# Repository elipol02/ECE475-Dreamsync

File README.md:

# Dreamsync

## Project Overview
Our product Dreamsync is designed to enhance health monitoring by integrating sensors that track various metrics related to sleep quality and environmental conditions. Data collected from the sensors are transmitted to a companion mobile application via Bluetooth for analysis and visualization. This will make it easier for our users to track their sleeping patterns.

### Features
- **Sleep Movement Monitoring**: Tracks body movements during sleep using an MPU6050 accelerometer and gyroscope.
- **Heart Rate Monitoring**: Continuously monitors heart rate using a photoplethysmography (PPG) sensor.
- **Environmental Light Exposure**: Measures light levels in the sleep environment using light sensors.
- **Ambient Temperature Monitoring**: Tracks the ambient temperature using a DS18B20 temperature sensor.
- **Battery Monitoring**: Measures battery voltage, percentage, and charging status.
- **Bluetooth Connectivity**: Transmits real-time sensor data to a companion app via BLE (Bluetooth Low Energy).

---

## Components and Dependencies

### Hardware Components
- **MPU6050**: Accelerometer and gyroscope for motion tracking.
- **DS18B20**: Temperature sensor.
- **PPG Sensor**: For heart rate monitoring.
- **Light Sensors**: Measures light levels (connected to analog pins A0 and A1).
- **nRF52840 Feather**: For Bluetooth communication.
- **LED**: Visual feedback for heart rate peaks.

### Software Libraries
- **Wire**: I2C communication with MPU6050.
- **OneWire**: Communication protocol for DS18B20.
- **DallasTemperature**: Interface for DS18B20 temperature sensor.
- **Adafruit Bluefruit**: Bluetooth communication.
- **Adafruit LittleFS**: Internal file system for configuration storage.

---

## Setup Instructions

### Hardware Setup
1. Connect the **MPU6050** to the I2C pins (SDA, SCL).
2. Attach the **DS18B20** sensor to `TEMP_SENSOR_PIN` (A2).
3. Connect **PPG Sensor** to `HEART_RATE_PIN` (A3).
4. Connect light sensors to `LIGHT_SENSOR_1` (A0) and `LIGHT_SENSOR_2` (A1).
5. Connect the LED to `LED_PIN` (3).

### Software Setup
1. You'll need to install the libraries we listed above.
2. Upload the firmware code provided to your nRF52840 development board via Arduino IDE.

### Mobile Application
1. Ensure the Bluetooth is enabled on your mobile device.
2. Pair with the "SleepMask" device via BLE.
3. Use the companion app to visualize and analyze the collected data.

---

## Code Highlights

### Key Functions
- **`initializeMPU6050()`**: Initializes the MPU6050 for motion tracking.
- **`readLightAndTemp()`**: Reads ambient light and temperature values.
- **`readHeartRateSensor()`**: Reads and processes heart rate data.
- **`calculateBPM()`**: Calculates beats per minute (BPM) based on PPG data.
- **`sendEnvironmentalData()`**: Sends light and temperature data over BLE.
- **`checkBattery()`**: Monitors battery voltage and percentage.
- **`startAdv()`**: Configures and starts BLE advertising.

### BLE Services
- **Device Information Service**: Provides metadata about the device.
- **UART Service**: Transmits sensor data to the mobile app.
- **Battery Service**: Sends battery status updates.

---

## Sensor Data Format

The sensor data is transmitted to the companion app in the following format:
1. **Environmental Data**: `E,light1,light2,temperature`
2. **Heart Rate Data**: `H,heartRate`
3. **Motion Data**: `M,accelX,accelY,accelZ,gyroX,gyroY,gyroZ,pitch,roll,motionIntensity`
4. **Battery Data**: `B,batteryVoltage,batteryPercent,isCharging`

---

## Contributors

Chukwuemeka Mordi, Chu-en Chang, Elijah Pollack, Kinner Parikh

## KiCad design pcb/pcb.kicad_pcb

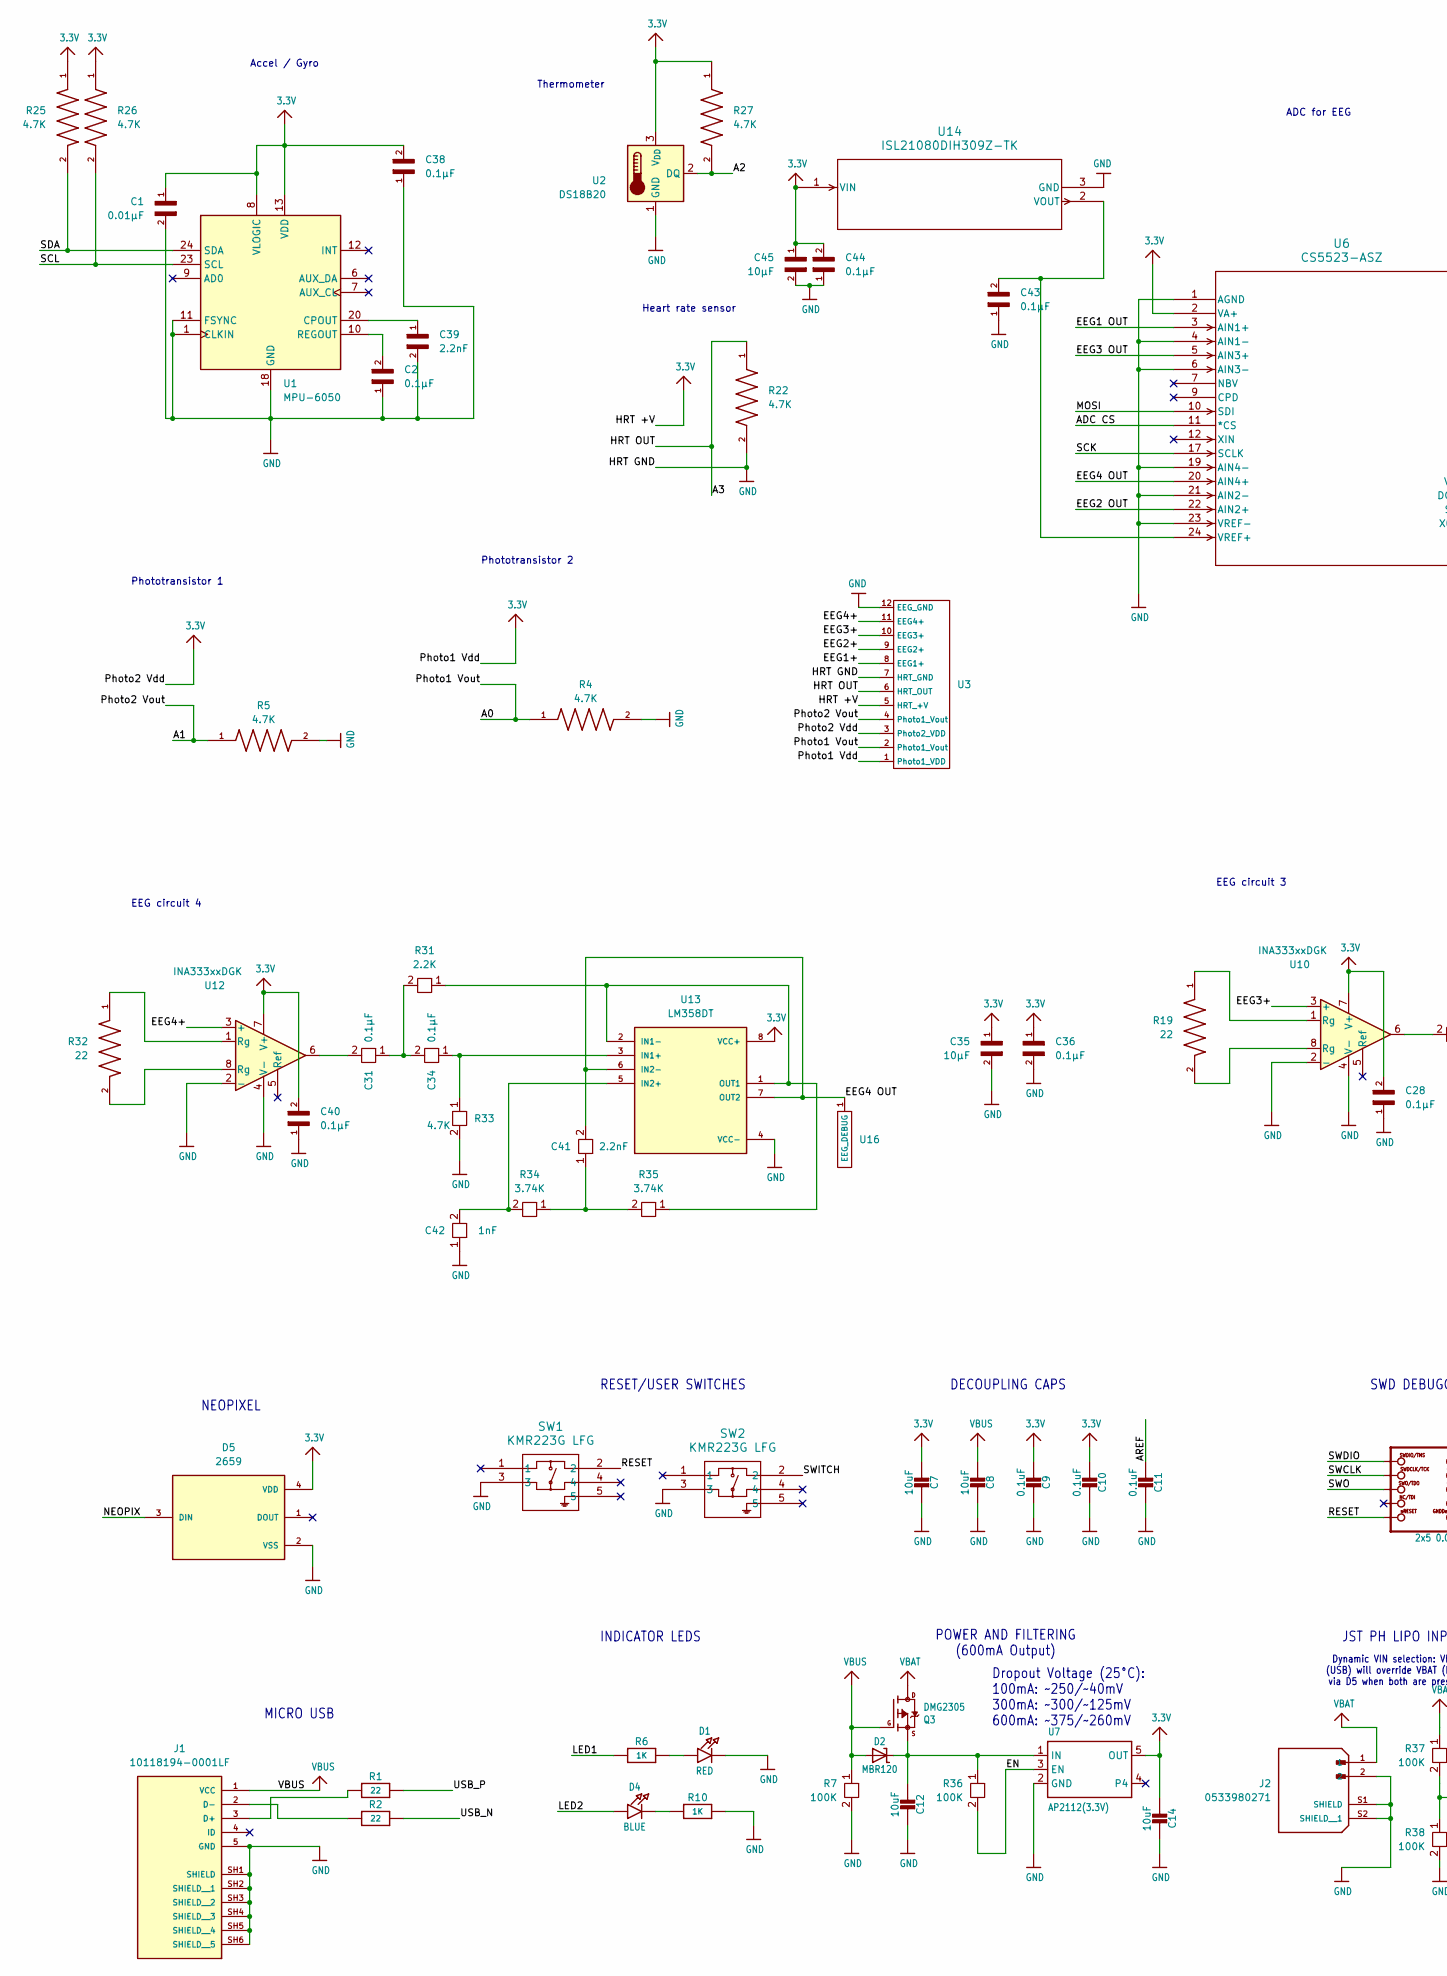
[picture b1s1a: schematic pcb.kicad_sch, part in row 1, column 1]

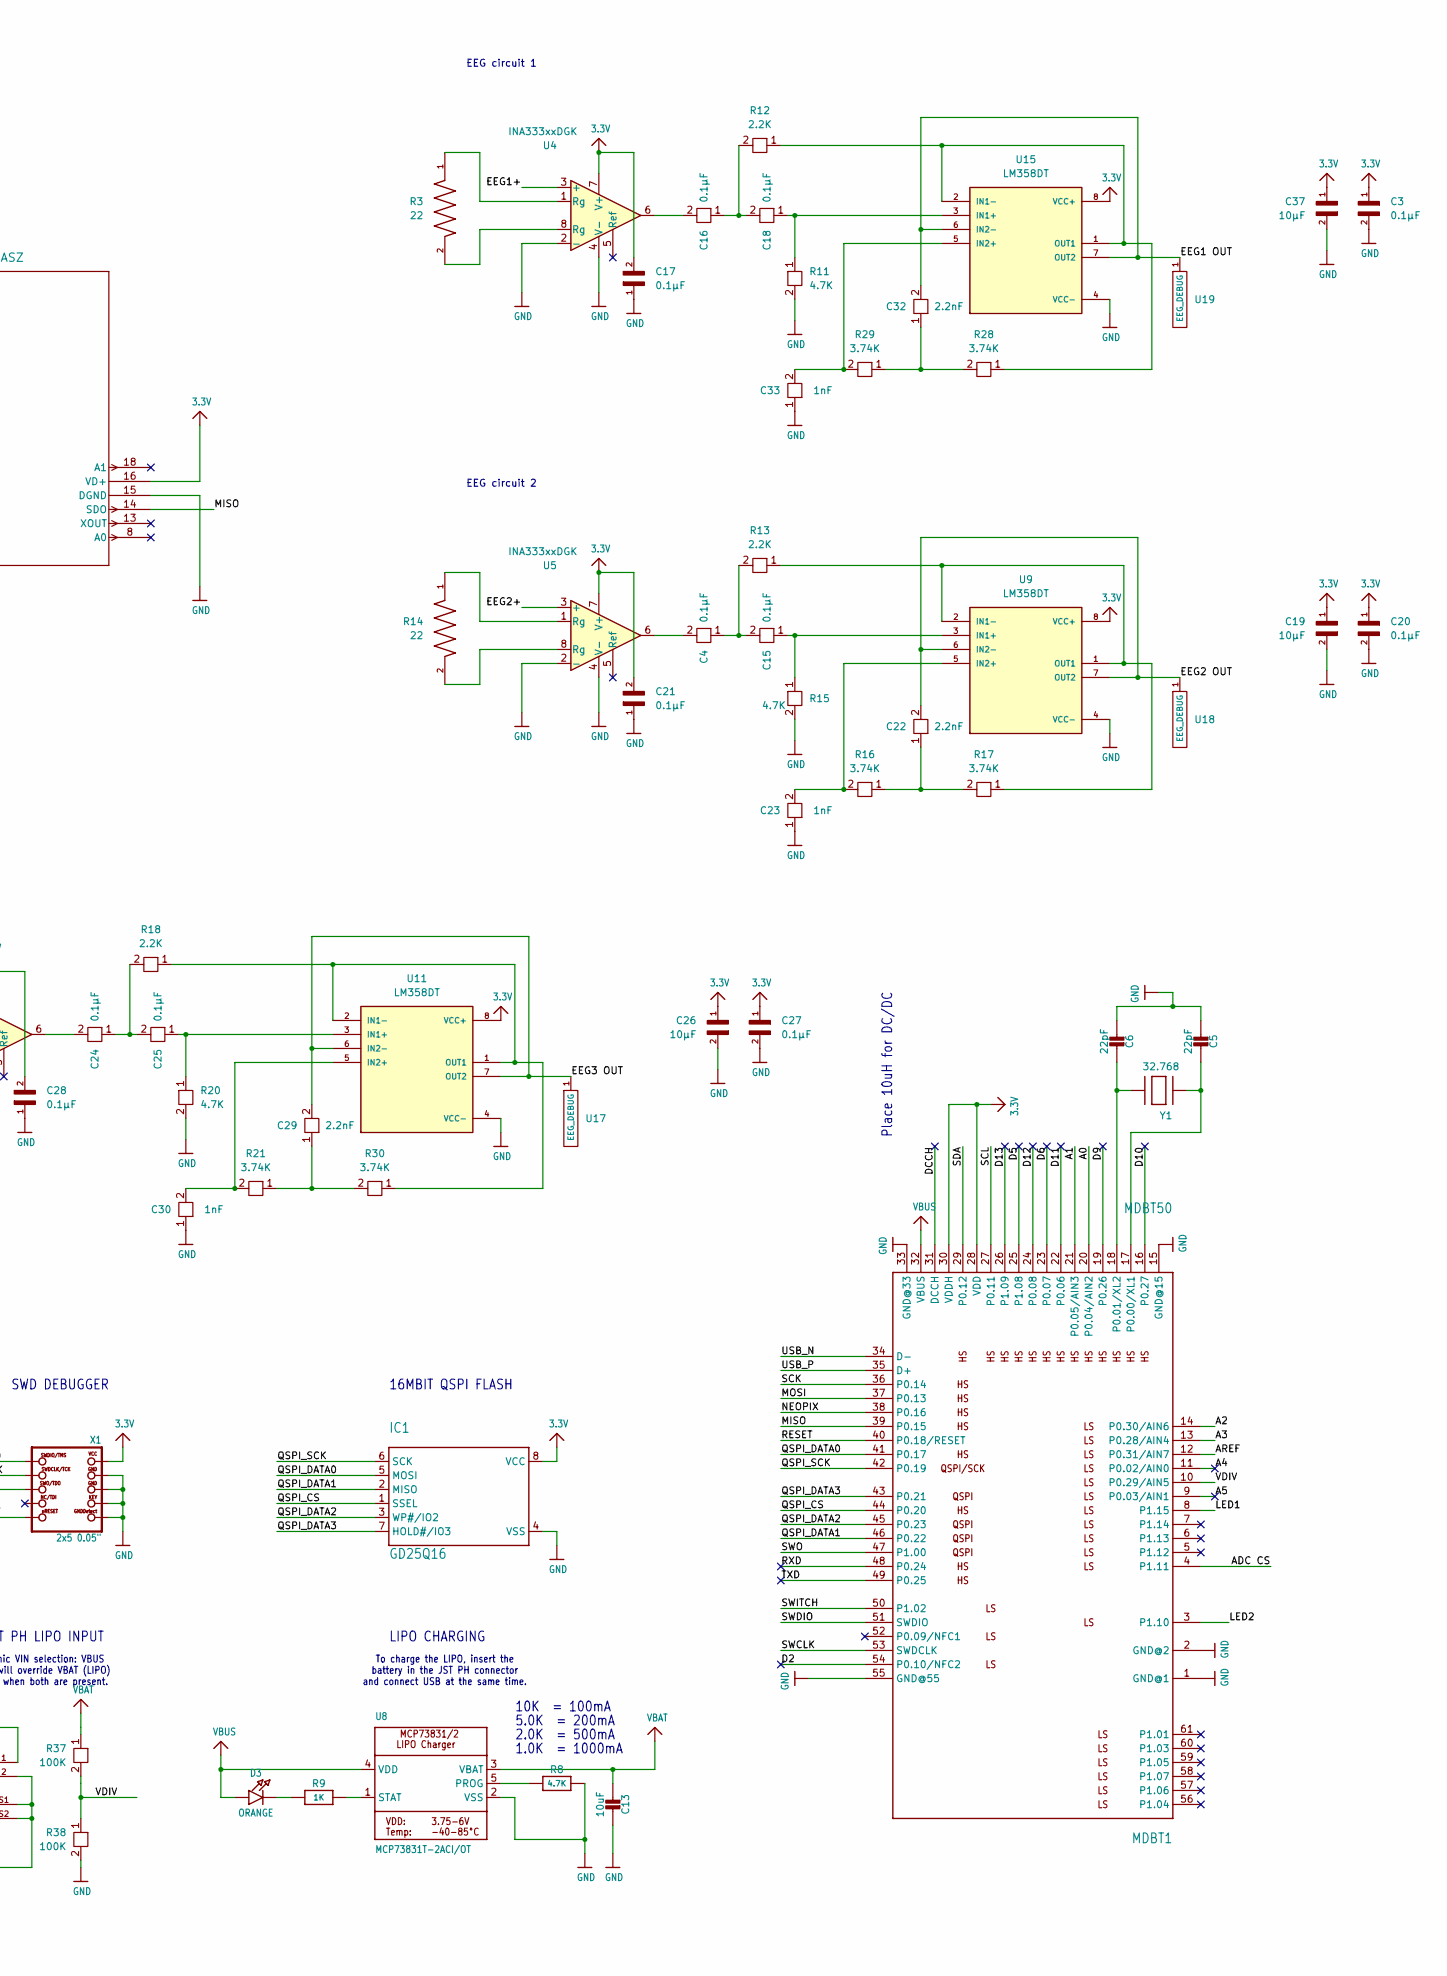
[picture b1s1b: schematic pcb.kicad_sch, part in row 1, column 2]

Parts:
C1: 0.01μF; CAPC2012X95N
C2, C3, C4, C15, C16, C17, C18, C20, C21, C24, C25, C27, C28, C31, C34, C36, C38, C40, C43, C44: 0.1μF; CAPC2012X88N
C5, C6: 22pF; CAPC220145_88N_KEM
C7, C8, C12, C13, C14: 10uF; CAPC2012X88N
C9, C10, C11: 0.1uF; CAPC2012X88N
C19, C26, C35, C37, C45: 10μF; CAPC2012X88N
C22, C29, C32, C39, C41: 2.2nF; CAP_CL21_SAM
C23, C30, C33, C42: 1nF; CAP_0805J_AVX
D1: RED; WL-SMCW_0805
D2: MBR120; SDO_SOD-123FL498_OSI
D3: ORANGE; WL-SMCW_0805
D4: BLUE; WL-SMCW_0805
D5: 2659; PARTREV 01
IC1: GD25Q16; SOIC127P600X175-8N
J1: 10118194-0001LF; AMPHENOL_10118194-0001LF; PARTREV D
J2: 0533980271; MOLEX_0533980271; PARTREV A
MDBT1: MDBT50; MDBT50Q-U
Q3: DMG2305; SOT91P240X110-3N_DMG2305UX-7
R1, R2, R3, R14, R19, R32: 22; RESC2012X60N
R4, R5, R22, R25, R26, R27: 4.7K; RESC2012X60N; DigiKey_Part_Number 311-4.7KJRTR-ND
R6, R9, R10: 1K; RESC2012X60N
R7, R36, R37, R38: 100K; RESC2012X60N
R8, R11, R15, R20, R33: 4.7K; RESC2012X60N
R12, R13, R18, R31: 2.2K; RESC2012X60N
R16, R17, R21, R28, R29, R30, R34, R35: 3.74K; RESC2012X60N
SW1, SW2: KMR223G LFG; KMR2_G_CNK
U1: MPU-6050; InvenSense_QFN-24_4x4mm_P0.5mm
U2: DS18B20; TO-92_Inline
U3: Sensors
U4, U5, U10, U12: INA333xxDGK; SOP65P490X110-8N
U6: CS5523-ASZ; CIR-SSOP-24
U7: AP2112(3.3V); SOT_RG1_DIO
U8: MCP73831T-2ACI/OT; SOT-23-5_MC_MCH
U9, U11, U13, U15: LM358DT; SOIC127P600X175-8N
U14: ISL21080DIH309Z-TK; P3_064_INR
U16, U17, U18, U19: EEG_DEBUG
X1: 2x5 0.05"; 2X05_1.27MM_BOX_POSTS
Y1: 32.768; XTAL_SC32S-7PF20PPM_EPS

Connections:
3.3V: C1.1, C3.1, C7.2, C9.2, C10.2, C14.2, C17.2, C19.1, C20.1, C21.2, C26.1, C27.1, C28.2, C35.1, C36.1, C37.1, C38.2, C40.2, C44.2, C45.1, D5.4 (VDD), IC1.8 (VCC), MDBT1.28 (VDD), MDBT1.30 (VDDH), R25.1, R26.1, R27.1, U1.8 (VLOGIC), U1.13 (VDD), U2.3 (V_{DD}), U3.1 (Photo1_VDD), U3.3 (Photo2_VDD), U3.5 (HRT_+V), U4.7 (V+), U5.7 (V+), U6.2 (VA+), U6.16 (VD+), U7.5 (OUT), U9.8 (VCC+), U10.7 (V+), U11.8 (VCC+), U12.7 (V+), U13.8 (VCC+), U14.1 (VIN), U15.8 (VCC+), X1.1 (VCC)
/A0: MDBT1.20 (P0.04/AIN2), R4.1, U3.2 (Photo1_Vout)
/A1: MDBT1.21 (P0.05/AIN3), R5.1, U3.4 (Photo1_Vout)
/A2: MDBT1.14 (P0.30/AIN6), R27.2, U2.2 (DQ)
/A3: MDBT1.13 (P0.28/AIN4), R22.1, U3.6 (HRT_OUT)
/A4: MDBT1.11 (P0.02/AIN0)
/A5: MDBT1.9 (P0.03/AIN1)
/ADC CS: MDBT1.4 (P1.11), U6.11 (*CS)
/AREF: C11.2, MDBT1.12 (P0.31/AIN7)
/D2: MDBT1.54 (P0.10/NFC2)
/D5: MDBT1.25 (P1.08)
/D6: MDBT1.23 (P0.07)
/D9: MDBT1.19 (P0.26)
/D10: MDBT1.16 (P0.27)
/D11: MDBT1.22 (P0.06)
/D12: MDBT1.24 (P0.08)
/D13: MDBT1.26 (P1.09)
/DCCH: MDBT1.31 (DCCH)
/EEG1 OUT: C32.2, U6.3 (AIN1+), U15.6 (IN2-), U15.7 (OUT2), U19.1 (EEG_DEBUG)
/EEG1+: U3.8 (EEG1+), U4.3 (+)
/EEG2 OUT: C22.2, U6.22 (AIN2+), U9.6 (IN2-), U9.7 (OUT2), U18.1 (EEG_DEBUG)
/EEG2+: U3.9 (EEG2+), U5.3 (+)
/EEG3 OUT: C29.2, U6.5 (AIN3+), U11.6 (IN2-), U11.7 (OUT2), U17.1 (EEG_DEBUG)
/EEG3+: U3.10 (EEG3+), U10.3 (+)
/EEG4 OUT: C41.2, U6.20 (AIN4+), U13.6 (IN2-), U13.7 (OUT2), U16.1 (EEG_DEBUG)
/EEG4+: U3.11 (EEG4+), U12.3 (+)
/EN: R36.2, U7.3 (EN)
/LED1: MDBT1.8 (P1.15), R6.1
/LED2: D4.A, MDBT1.3 (P1.10)
/MISO: MDBT1.39 (P0.15), U6.14 (SDO)
/MOSI: MDBT1.37 (P0.13), U6.10 (SDI)
/NEOPIX: D5.3 (DIN), MDBT1.38 (P0.16)
/QSPI_CS: IC1.1 (SSEL), MDBT1.44 (P0.20)
/QSPI_DATA0: IC1.5 (MOSI), MDBT1.41 (P0.17)
/QSPI_DATA1: IC1.2 (MISO), MDBT1.46 (P0.22)
/QSPI_DATA2: IC1.3 (WP#/IO2), MDBT1.45 (P0.23)
/QSPI_DATA3: IC1.7 (HOLD#/IO3), MDBT1.43 (P0.21)
/QSPI_SCK: IC1.6 (SCK), MDBT1.42 (P0.19)
/RESET: MDBT1.40 (P0.18/RESET), SW1.2, X1.10 (NRESET)
/RXD: MDBT1.48 (P0.24)
/SCK: MDBT1.36 (P0.14), U6.17 (SCLK)
/SCL: MDBT1.27 (P0.11), R26.2, U1.23 (SCL)
/SDA: MDBT1.29 (P0.12), R25.2, U1.24 (SDA)
/SWCLK: MDBT1.53 (SWDCLK), X1.4 (SWDCLK)
/SWDIO: MDBT1.51 (SWDIO), X1.2 (SWDIO)
/SWITCH: MDBT1.50 (P1.02), SW2.2
/SWO: MDBT1.47 (P1.00), X1.6 (SWO)
/TXD: MDBT1.49 (P0.25)
/USB_N: MDBT1.34 (D-), R2.2
/USB_P: MDBT1.35 (D+), R1.2
/VDIV: MDBT1.10 (P0.29/AIN5), R37.2, R38.1
GND: C1.2, C2.1, C3.2, C5.2, C6.2, C7.1, C8.1, C9.1, C10.1, C11.1, C12.1, C13.1, C14.1, C17.1, C19.2, C20.2, C21.1, C23.1, C26.2, C27.2, C28.1, C30.1, C33.1, C35.2, C36.2, C37.2, C38.1, C39.2, C40.1, C42.1, C43.1, C44.1, C45.2, D1.C, D5.2 (VSS), IC1.4 (VSS), J1.5 (GND), J1.SH1 (SHIELD), J1.SH2 (SHIELD__1), J1.SH3 (SHIELD__2), J1.SH4 (SHIELD__3), J1.SH5 (SHIELD__4), J1.SH6 (SHIELD__5), J2.2, J2.S1 (SHIELD), J2.S2 (SHIELD__1), MDBT1.1 (GND@1), MDBT1.2 (GND@2), MDBT1.15 (GND@15), MDBT1.33 (GND@33), MDBT1.55 (GND@55), R4.2, R5.2, R7.2, R8.2, R10.2, R11.2, R15.2, R20.2, R22.2, R33.2, R38.2, SW1.3, SW2.3, U1.1 (CLKIN), U1.11 (FSYNC), U1.18 (GND), U2.1 (GND), U3.7 (HRT_GND), U3.12 (EEG_GND), U4.2 (-), U4.4 (V-), U5.2 (-), U5.4 (V-), U6.1 (AGND), U6.4 (AIN1-), U6.6 (AIN3-), U6.15 (DGND), U6.19 (AIN4-), U6.21 (AIN2-), U6.23 (VREF-), U7.2 (GND), U8.2 (VSS), U9.4 (VCC-), U10.2 (-), U10.4 (V-), U11.4 (VCC-), U12.2 (-), U12.4 (V-), U13.4 (VCC-), U14.3 (GND), U15.4 (VCC-), X1.3 (GND@1), X1.5 (GND@2), X1.7 (KEY), X1.9 (GNDDETECT)
unnamed: C4.2, U5.6
unnamed: C4.1, C15.2, R13.2
unnamed: C16.1, C18.2, R12.2
unnamed: C16.2, U4.6
unnamed: C22.1, R16.1, R17.2
unnamed: C24.1, C25.2, R18.2
unnamed: C24.2, U10.6
unnamed: C29.1, R21.1, R30.2
unnamed: C31.1, C34.2, R31.2
unnamed: C31.2, U12.6
unnamed: C32.1, R28.2, R29.1
unnamed: C41.1, R34.1, R35.2
unnamed: D1.A, R6.2
unnamed: D3.C, R9.1
unnamed: D4.C, R10.1
unnamed: J1.3 (D+), R1.1
unnamed: J1.2 (D-), R2.1
unnamed: C5.1, MDBT1.17 (P0.00/XL1), Y1.1
unnamed: C6.1, MDBT1.18 (P0.01/XL2), Y1.2
unnamed: C12.2, D2.C, Q3.2 (S), R36.1, U7.1 (IN)
unnamed: R3.1, U4.1 (Rg)
unnamed: R3.2, U4.8 (Rg)
unnamed: R14.1, U5.1 (Rg)
unnamed: R14.2, U5.8 (Rg)
unnamed: R19.1, U10.1 (Rg)
unnamed: R19.2, U10.8 (Rg)
unnamed: R32.1, U12.1 (Rg)
unnamed: R32.2, U12.8 (Rg)
unnamed: C39.1, U1.20 (CPOUT)
unnamed: C2.2, U1.10 (REGOUT)
unnamed: R8.1, U8.5 (PROG)
unnamed: R9.2, U8.1 (STAT)
unnamed: C15.1, R15.1, U9.3 (IN1+)
unnamed: R13.1, R17.1, U9.1 (OUT1), U9.2 (IN1-)
unnamed: C23.2, R16.2, U9.5 (IN2+)
unnamed: C25.1, R20.1, U11.3 (IN1+)
unnamed: R18.1, R30.1, U11.1 (OUT1), U11.2 (IN1-)
unnamed: C30.2, R21.2, U11.5 (IN2+)
unnamed: C34.1, R33.1, U13.3 (IN1+)
unnamed: R31.1, R35.1, U13.1 (OUT1), U13.2 (IN1-)
unnamed: C42.2, R34.2, U13.5 (IN2+)
unnamed: C43.2, U6.24 (VREF+), U14.2 (VOUT)
unnamed: C18.1, R11.1, U15.3 (IN1+)
unnamed: R12.1, R28.1, U15.1 (OUT1), U15.2 (IN1-)
unnamed: C33.2, R29.2, U15.5 (IN2+)
VBAT: C13.2, J2.1, Q3.3 (D), R37.1, U8.3 (VBAT)
VBUS: C8.2, D2.A, D3.A, J1.1 (VCC), MDBT1.32 (VBUS), Q3.1 (G), R7.1, U8.4 (VDD)

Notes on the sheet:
EEG circuit 3
SWD DEBUGGER
EEG circuit 2
LIPO CHARGING
JST PH LIPO INPUT
To charge the LIPO, insert the battery in the JST PH connector and connect USB at the same time.
Phototransistor 1
Place 10uH for DC/DC
DECOUPLING CAPS
10K = 100mA
2.0K = 500mA
POWER AND FILTERING (600mA Output)
16MBIT QSPI FLASH
Thermometer
Phototransistor 2
Heart rate sensor
RESET/USER SWITCHES
1.0K = 1000mA
Dropout Voltage (25°C): 100mA: ~250/~40mV 300mA: ~300/~125mV 600mA: ~375/~260mV
EEG circuit 4
Dynamic VIN selection: VBUS (USB) will override VBAT (LIPO) via D5 when both are present.
NEOPIXEL
ADC for EEG
Accel / Gyro
INDICATOR LEDS
5.0K = 200mA
EEG circuit 1
MICRO USB

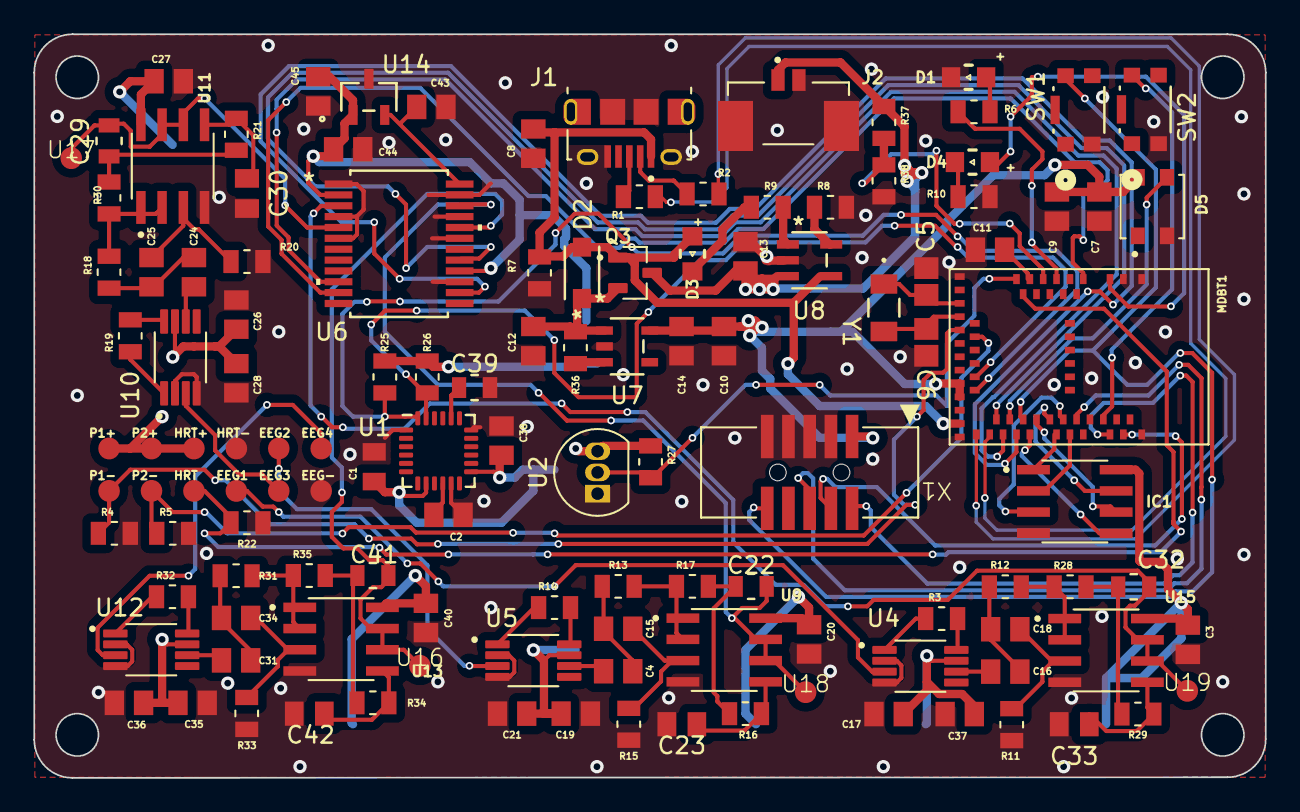
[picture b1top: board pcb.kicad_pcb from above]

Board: 2 copper layers, 73.7 x 44.5 mm, 114 parts (0 on the bottom side), 86 nets.

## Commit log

2024-10-25 created files
2024-11-01 battery and acceleration
2024-11-02 pcb update
2024-11-07 Add files via upload
    Joanne's part of code
2024-11-07 place sensor file in separate folder + fix case statements
2024-11-12 pcb sketch updates
2024-11-13 working code for the accelerometer
2024-11-14 added bluetooth functionality
2024-11-14 testing battery
2024-11-14 pcb updates
2024-12-03 just bringing it to our attention
2024-12-04 add the latest sensor_complete code
2024-12-04 cleaning up the files p1
2024-12-04 revamped readme
2024-12-04 rename sensor file and add 1 second version
2024-12-04 fixed formatting of the data again to remove words and duplicate reporting
2024-12-04 cleanup files part 2
2024-12-04 manual delete 1
2024-12-04 manual delete 2
2024-12-04 manual delete 3
2024-12-04 manual delete 4
2024-12-04 manual delete 5
2024-12-05 uncommented demo day code...
2024-12-05 adding reset to demo day to debug
2024-12-05 remove reset, it doesnt work
2024-12-08 changed bluetooth streaming
    bluetooth now sends each sensor data in its own packet one at a time, they are sent in json format
2024-12-17 adc testing
